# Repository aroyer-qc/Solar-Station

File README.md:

# SolarStation

ESP32-based solar station firmware for two-axis panel positioning, output scheduling, diagnostics, and network control. The firmware is designed for the Solar Station control PCB; its third stepper channel is currently unused by this project.

## Current Status

The firmware is in an active integration phase.

Implemented and working in firmware:

- FastAccelStepper integration with the PCB's 3 available stepper channels.
- Axis control on real steppers:
	- Azimuth controller uses Stepper1.
	- Elevation controller uses Stepper2.
	- Stepper3 is currently unused and available for future or other control applications.
- Configurable axis parameters (persisted):
	- Min/max angle limits.
	- Steps-per-degree ratio.
	- Step speed and acceleration.
- Portal dashboard + configuration UI (`/` and `/portal`) with sections for:
	- Solar tracking settings.
	- Axis settings.
	- Wi-Fi and NTP.
	- Output manual/auto control and schedules.
	- Hardware diagnostics (limit switches, driver DIAG, currents, sunrise/sunset).
- Output scheduler (3 outputs) with:
	- Fixed time or sunrise/sunset windows.
	- Duty cycle control.
	- AUTO/MANUAL mode per output.
- Wi-Fi behavior:
	- STA when configured.
	- AP fallback/setup mode when STA is not configured or fails.
- Sunset return preposition behavior:
	- Always active.
	- Executes once per target day.
	- Uses a fixed delay after local sunset before prepositioning to next sunrise target.
- Diagnostics override workflow:
	- Dedicated page (`/diag` and `/portal/diag`) to force azimuth/elevation for testing.
	- Canceling test mode returns panel to current calculated solar position.

## Testing Without Optional Hardware

The firmware includes compile-time switches for testing on an ESP32 without all of the connected hardware. In `Solar-Station.ino`, set any unavailable hardware feature to `0` before compiling:

```cpp
#define USE_BH1750_SENSOR 0  // Disable the BH1750 light sensor
#define USE_IO_EXPANDER   0  // Disable the PCA9538 I2C I/O expander
#define USE_M95P32        0  // Disable the M95P32 external SPI EEPROM
```

Available hardware switches:

- `USE_BH1750_SENSOR`: BH1750 light sensor support; default is `1`.
- `USE_IO_EXPANDER`: PCA9538 I2C I/O expander support; default is `1`.
- `USE_M95P32`: M95P32 external SPI EEPROM support; default is `1`.

Disable only the hardware that is not connected. With a feature disabled, its driver is excluded from the build and the related initialization and access code is skipped. The ESP32, firmware logic, web interface, and other enabled features can then be tested independently.

## Control PCB

The firmware is designed for the ESP32-based Solar Station control PCB shown below. The PCB can also be reused for other automation and control projects because it provides:

- Three stepper motor controller channels; this project uses two for azimuth and elevation, while the third is currently unused.
- Inputs for switches such as limit switches and other digital status signals.
- Three MOSFET-controlled outputs that use the connected 12 V to 36 V power supply.
- One I2C port.
- One communication port.
- 3.3 V logic levels for the I2C and communication ports.

Check the electrical requirements of each connected motor, switch, and load before use. The MOSFET outputs switch the board's power-supply voltage, while the I2C and communication interfaces use 3.3 V logic.

## Hardware Notes (Current Wiring Assumptions)

- MCU: ESP32.
- Stepper drivers: TMC2209 (3 channels; two used by this project, one available).
- I/O expander: PCA9538 (I2C) for shared microstep pins, status LED, and limit switch inputs.
- External SPI EEPROM module support included (`M95PxxModule`).

## Main Runtime Modules

- `Solar-Station.ino`: orchestration, hardware init, scheduler, diagnostics helpers, sunset return, test override state.
- `ConfigModule.h` / `ConfigModule.ino`: persisted configuration storage and defaults.
- `AzimuthController.*`: azimuth axis control on FastAccelStepper.
- `ElevationController.*`: elevation axis control on FastAccelStepper.
- `WebServerModule.*`: synchronous web server routes and HTML placeholder binding.
- `WifiModule.*`: STA/AP behavior and reconnect strategy.
- `portal/index.html`: AP/setup portal page.
- `portal/diag.html`: diagnostics override page.
- `console/index.html`: full network console page.

Web UI deployment model:

- Local UI files are served from device filesystem (LittleFS/SPIFFS data partition).
- Use the `data` folder content and upload it with `tools/upload_spiffs.ps1` after firmware upload.
- Filesystem layout:
	- `data/portal/*` for AP/setup pages.
	- `data/console/*` for full network console pages.

## Web Endpoints (Current)

Main pages:

- `GET /` main dashboard/configuration page.
- `GET /portal` AP/setup portal page.
- `GET /diag` diagnostics test page.
- `GET /portal/diag` diagnostics test page.
- `GET /console` full network console page.
- `GET /diag/status` plain-text status snapshot for diagnostics page refresh.

Tracking diagnostics actions:

- `POST /setTrackingOverride` (form fields: `azimuth`, `elevation`).
- `POST /cancelTrackingOverride`.

Configuration actions (examples):

- `POST /saveSolarTrackingConfig`
- `POST /saveAzimuthConfig`
- `POST /saveElevationConfig`
- `POST /saveNTPConfig`
- `POST /saveWiFiConfig`
- `POST /saveScheduleConfig`

## Configuration Persistence

Configuration is stored with ESP32 Preferences.

- Main configuration uses a raw blob (`ConfigData_t`).
- Output AUTO/MANUAL flags are stored in separate keys (`out_auto_0..2`).

Important:

- Any structural change to `ConfigData_t` size causes existing blob data to be considered incompatible and defaults are restored on next boot.

## Build Portability (Another PC)

This project now includes the async network libraries in the project `libraries` folder, so the same code and patches follow the project:

- `libraries/ESPAsyncWebServer` (v3.1.0, with local compatibility patches)
- `libraries/AsyncTCP` (v1.1.4)
- `libraries/ESPAsyncTCP`

To build on another computer:

1. Install Arduino IDE 2.x.
2. Install `esp32` board platform in Boards Manager.
3. Open `Solar-Station.ino` from this project folder (do not copy only the `.ino` file).
4. Compile directly; do not install another conflicting `ESPAsyncWebServer` manually unless you intentionally want to replace the bundled one.

Recommended:

- If you already have other async web libraries globally installed in your Arduino libraries folder, keep versions aligned with this project to avoid API/link mismatches.

## Known Limitations / Work In Progress

- Legacy configuration compatibility paths and placeholder-based HTML binding remain in the codebase.
- Arduino IntelliSense can report false compile errors in editor context even when firmware logic is valid.
- Full production solar tracking loop policy (beyond targeted move and preposition behavior) may still need refinement for final deployment scenarios.

## Quick Validation Checklist

- Open `/` and verify dashboard values update.
- Confirm Wi-Fi mode (STA or AP fallback) is shown correctly.
- In configuration tabs, set axis limits/ratio/speed/acceleration and save.
- Use `/diag`:
	- Apply manual override.
	- Cancel test and verify return to current calculated position.
- Verify sunset return preposition occurs after sunset + fixed delay.

## License

This project is released under the [MIT License](https://opensource.org/license/mit/).

Project files contain their own headers where applicable.

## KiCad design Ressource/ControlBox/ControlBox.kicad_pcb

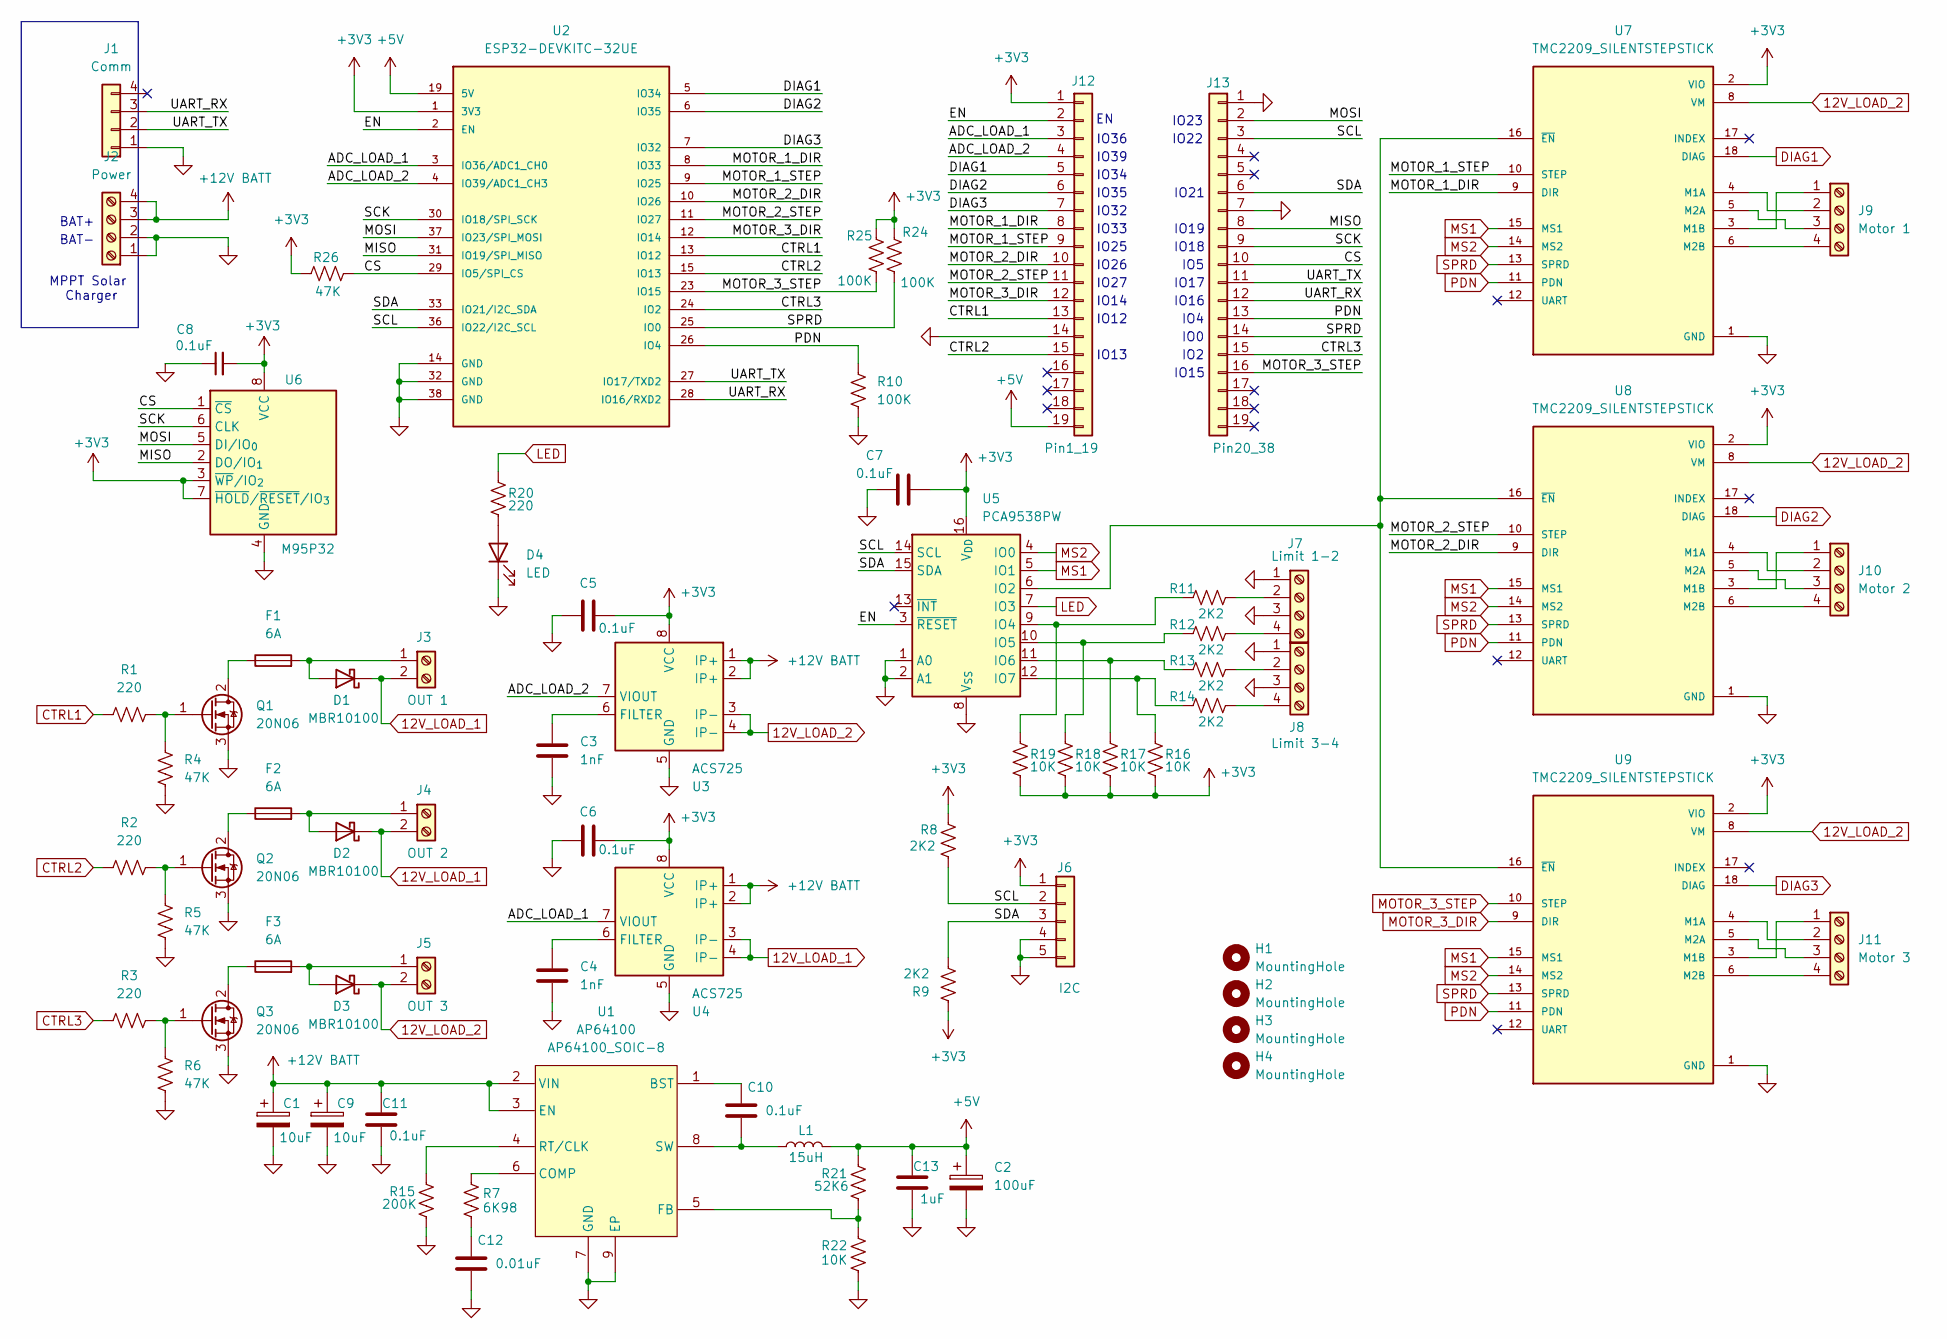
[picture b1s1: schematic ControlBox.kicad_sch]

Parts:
C1, C9: 10uF; CP_Elec_6.3x5.4
C2: 100uF; CP_Elec_8x6.7
C3, C4: 1nF; C_0805_2012Metric_Pad1.18x1.45mm_HandSolder
C5, C6, C7, C8, C10, C11: 0.1uF; C_0805_2012Metric_Pad1.18x1.45mm_HandSolder
C12: 0.01uF; C_0805_2012Metric_Pad1.18x1.45mm_HandSolder
C13: 1uF; C_0805_2012Metric_Pad1.18x1.45mm_HandSolder
D1, D2, D3: MBR10100; TO-220-2_Vertical
D4: LED; LED_D4.0mm
F1, F2, F3: 6A; Fuseholder_Clip-4x15mm_Generic_Horizontal
H1, H2, H3, H4: MountingHole; MountingHole_2.7mm_M2.5
J1: Comm; JST_EH_B4B-EH-A_1x04_P2.50mm_Vertical
J2: Power; TerminalBlock_CUI_TB007-508-04_1x04_P5.08mm_Horizontal
J3: OUT 1; TerminalBlock_CUI_TB007-508-02_1x02_P5.08mm_Horizontal
J4: OUT 2; TerminalBlock_CUI_TB007-508-02_1x02_P5.08mm_Horizontal
J5: OUT 3; TerminalBlock_CUI_TB007-508-02_1x02_P5.08mm_Horizontal
J6: I2C; JST_EH_B5B-EH-A_1x05_P2.50mm_Vertical
J7: Limit 1-2; TerminalBlock_CUI_TB007-508-04_1x04_P5.08mm_Horizontal
J8: Limit 3-4; TerminalBlock_CUI_TB007-508-04_1x04_P5.08mm_Horizontal
J9: Motor 1; TerminalBlock_CUI_TB007-508-04_1x04_P5.08mm_Horizontal
J10: Motor 2; TerminalBlock_CUI_TB007-508-04_1x04_P5.08mm_Horizontal
J11: Motor 3; TerminalBlock_CUI_TB007-508-04_1x04_P5.08mm_Horizontal
J12: Pin1_19; PinHeader_1x19_P2.54mm_Vertical
J13: Pin20_38; PinHeader_1x19_P2.54mm_Vertical
L1: 15uH; L_Bourns_SRP1038C_10.0x10.0mm
Q1, Q2, Q3: 20N06; TO-252-2
R1, R2, R3, R20: 220; R_0805_2012Metric_Pad1.20x1.40mm_HandSolder
R4, R5, R6, R26: 47K; R_0805_2012Metric_Pad1.20x1.40mm_HandSolder
R7: 6K98; R_0805_2012Metric_Pad1.20x1.40mm_HandSolder
R8, R9, R11, R12, R13, R14: 2K2; R_0805_2012Metric_Pad1.20x1.40mm_HandSolder
R10, R24, R25: 100K; R_0805_2012Metric_Pad1.20x1.40mm_HandSolder
R15: 200K; R_0805_2012Metric_Pad1.20x1.40mm_HandSolder
R16, R17, R18, R19, R22: 10K; R_0805_2012Metric_Pad1.20x1.40mm_HandSolder
R21: 52K6; R_0805_2012Metric_Pad1.20x1.40mm_HandSolder
U1: AP64100; AP64100_SOIC-8
U2: ESP32-DEVKITC-32UE; PARTREV V4
U3, U4: ACS725; SOIC-8_3.9x4.9mm_P1.27mm
U5: PCA9538PW; TSSOP-16_4.4x5mm_P0.65mm
U6: M95P32; SOIC-8_5.3x5.3mm_P1.27mm
U7, U8, U9: TMC2209_SILENTSTEPSTICK; MOD_TMC2209; PARTREV 1.20

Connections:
12V_LOAD_1: D1.1 (K), D2.1 (K), J3.2, J4.2, U4.3 (IP-), U4.4 (IP-)
12V_LOAD_2: D3.1 (K), J5.2, U3.3 (IP-), U3.4 (IP-), U7.8 (VM), U8.8 (VM), U9.8 (VM)
+3V3: C5.2, C6.2, C7.2, C8.2, J6.1, J12.1, R8.1, R9.1, R16.2, R17.2, R18.2, R19.2, R24.1, R25.1, R26.1, U2.1 (3V3), U3.8 (VCC), U4.8 (VCC), U5.16 (V_{DD}), U6.3 (~WP/IO_{2}), U6.7 (~HOLD/~RESET/IO_{3}), U6.8 (VCC), U7.2 (VIO), U8.2 (VIO), U9.2 (VIO)
+5V: C2.1, C13.1, J12.19, L1.2, R21.1, U2.19 (5V)
+12V BATT: C1.1, C9.1, C11.1, J2.3, J2.4, U1.2 (VIN), U1.3 (EN), U3.1 (IP+), U3.2 (IP+), U4.1 (IP+), U4.2 (IP+)
/ADC_LOAD_1: J12.3, U2.3 (IO36/ADC1_CH0), U4.7 (VIOUT)
/ADC_LOAD_2: J12.4, U2.4 (IO39/ADC1_CH3), U3.7 (VIOUT)
/CS: J13.10, R26.2, U2.29 (IO5/SPI_CS), U6.1 (~CS)
/EN: J12.2, U2.2 (EN), U5.3 (~RESET)
/MISO: J13.8, U2.31 (IO19/SPI_MISO), U6.2 (DO/IO_{1})
/MOSI: J13.2, U2.37 (IO23/SPI_MOSI), U6.5 (DI/IO_{0})
/MOTOR_1_DIR: J12.8, U2.8 (IO33), U7.9 (DIR)
/MOTOR_1_STEP: J12.9, U2.9 (IO25), U7.10 (STEP)
/MOTOR_2_DIR: J12.10, U2.10 (IO26), U8.9 (DIR)
/MOTOR_2_STEP: J12.11, U2.11 (IO27), U8.10 (STEP)
/SCK: J13.9, U2.30 (IO18/SPI_SCK), U6.6 (CLK)
/SCL: J6.2, J13.3, R8.2, U2.36 (IO22/I2C_SCL), U5.14 (SCL)
/SDA: J6.3, J13.6, R9.2, U2.33 (IO21/I2C_SDA), U5.15 (SDA)
/UART_RX: J1.3, J13.12, U2.28 (IO16/RXD2)
/UART_TX: J1.2, J13.11, U2.27 (IO17/TXD2)
CTRL1: J12.13, R1.1, U2.13 (IO12)
CTRL2: J12.15, R2.1, U2.15 (IO13)
CTRL3: J13.15, R3.1, U2.24 (IO2)
DIAG1: J12.5, U2.5 (IO34), U7.18 (DIAG)
DIAG2: J12.6, U2.6 (IO35), U8.18 (DIAG)
DIAG3: J12.7, U2.7 (IO32), U9.18 (DIAG)
GND: C1.2, C2.2, C3.2, C4.2, C5.1, C6.1, C7.1, C8.1, C9.2, C11.2, C12.2, C13.2, D4.1 (K), J1.1, J2.1, J2.2, J6.4, J6.5, J7.1, J7.3, J8.1, J8.3, J12.14, J13.1, J13.7, Q1.3 (S), Q2.3 (S), Q3.3 (S), R4.2, R5.2, R6.2, R10.2, R15.2, R22.2, U1.7 (GND), U1.9 (EP), U2.14 (GND), U2.32 (GND), U2.38 (GND), U3.5 (GND), U4.5 (GND), U5.1 (A0), U5.2 (A1), U5.8 (V_{SS}), U6.4 (GND), U7.1 (GND), U7.7 (GND), U8.1 (GND), U8.7 (GND), U9.1 (GND), U9.7 (GND)
LED: R20.1, U5.7 (IO3)
MOTOR_3_DIR: J12.12, U2.12 (IO14), U9.9 (DIR)
MOTOR_3_STEP: J13.16, R25.2, U2.23 (IO15), U9.10 (STEP)
MS1: U5.5 (IO1), U7.15 (MS1), U8.15 (MS1), U9.15 (MS1)
MS2: U5.4 (IO0), U7.14 (MS2), U8.14 (MS2), U9.14 (MS2)
unnamed: C12.1, R7.2
unnamed: D1.2 (A), F1.2, J3.1
unnamed: D2.2 (A), F2.2, J4.1
unnamed: D3.2 (A), F3.2, J5.1
unnamed: D4.2 (A), R20.2
unnamed: J7.2, R11.2
unnamed: J7.4, R12.2
unnamed: J8.2, R13.2
unnamed: J8.4, R14.2
unnamed: J9.1, U7.3 (M1B)
unnamed: J9.2, U7.4 (M1A)
unnamed: J9.3, U7.5 (M2A)
unnamed: J9.4, U7.6 (M2B)
unnamed: J10.1, U8.3 (M1B)
unnamed: J10.2, U8.4 (M1A)
unnamed: J10.3, U8.5 (M2A)
unnamed: J10.4, U8.6 (M2B)
unnamed: J11.1, U9.3 (M1B)
unnamed: J11.2, U9.4 (M1A)
unnamed: J11.3, U9.5 (M2A)
unnamed: J11.4, U9.6 (M2B)
unnamed: F1.1, Q1.2 (D)
unnamed: Q1.1 (G), R1.2, R4.1
unnamed: F2.1, Q2.2 (D)
unnamed: Q2.1 (G), R2.2, R5.1
unnamed: F3.1, Q3.2 (D)
unnamed: Q3.1 (G), R3.2, R6.1
unnamed: C10.1, U1.1 (BST)
unnamed: R7.1, U1.6 (COMP)
unnamed: R21.2, R22.1, U1.5 (FB)
unnamed: R15.1, U1.4 (RT/CLK)
unnamed: C10.2, L1.1, U1.8 (SW)
unnamed: C3.1, U3.6 (FILTER)
unnamed: C4.1, U4.6 (FILTER)
unnamed: U5.6 (IO2), U7.16 (~EN), U8.16 (~EN), U9.16 (~EN)
unnamed: R11.1, R19.1, U5.9 (IO4)
unnamed: R12.1, R18.1, U5.10 (IO5)
unnamed: R13.1, R17.1, U5.11 (IO6)
unnamed: R14.1, R16.1, U5.12 (IO7)
PDN: J13.13, R10.1, U2.26 (IO4), U7.11 (PDN), U8.11 (PDN), U9.11 (PDN)
SPRD: J13.14, R24.2, U2.25 (IO0), U7.13 (SPRD), U8.13 (SPRD), U9.13 (SPRD)

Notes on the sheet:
IO32
IO27
IO17
MPPT Solar Charger
IO13
BAT-
IO36
IO21
IO18
IO14
IO25
IO26
IO0
IO34
IO19
IO35
IO15
IO2
IO4
IO16
IO33
IO22
IO5
IO12
IO23
IO39
BAT+

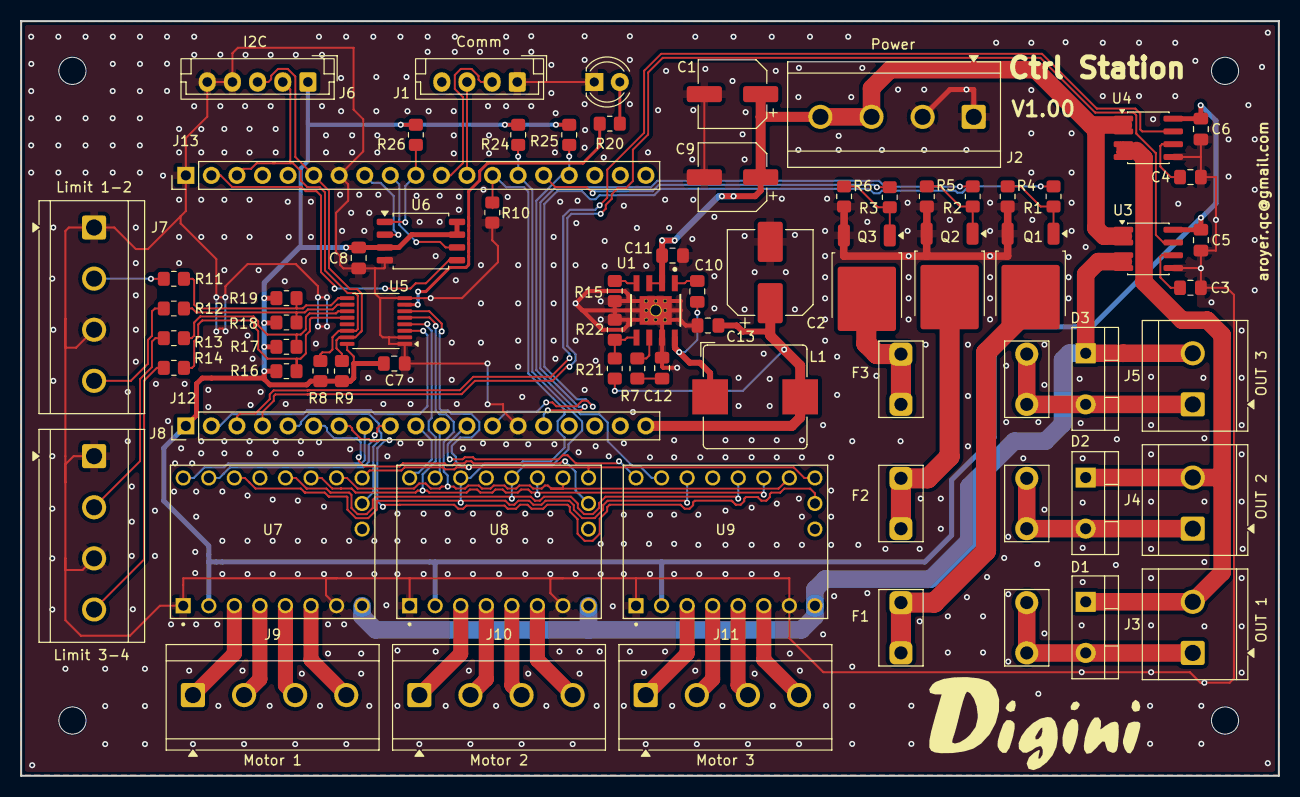
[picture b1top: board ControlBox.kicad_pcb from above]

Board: 2 copper layers, 125.0 x 75.0 mm, 74 parts (0 on the bottom side), 73 nets.
